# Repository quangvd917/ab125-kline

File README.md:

# AB125 K-Line: đọc dữ liệu ECU Honda Air Blade 125 (2023) qua giắc DLC

> **English summary.** DIY reader for the Honda K-Line diagnostic port on a Honda Air Blade 125 (2023, PGM-FI) scooter. An ESP32-C3 talks to the ECU through an L9637D transceiver, decodes RPM, speed, coolant/intake temperature, throttle and battery voltage from Honda table `0x17`, and shows them on a phone (WiFi web page) and on a 2.8" "Cheap Yellow Display" dashboard (ESP-NOW). Firmware (PlatformIO/Arduino), KiCad schematic + PCB, and the decoded protocol are all here. Docs are in Vietnamese.

## Tính năng
- Đọc **vòng tua, tốc độ, nhiệt độ máy, nhiệt độ khí nạp, độ mở bướm ga, điện áp ắc quy** khoảng 7 lần mỗi giây.
- **Trang web trên điện thoại:** kết nối WiFi `AB125`, mở `http://192.168.4.1`. Không cần cài app.
- **Đọc mã lỗi PGM-FI** (lỗi hiện tại và lỗi đã lưu) kèm mô tả tiếng Việt. Đã kiểm chứng bằng một lỗi thật tạo ra có chủ đích (8-1). Có nút **xóa lỗi** (đã thử thành công trên xe), chỉ hoạt động khi máy không nổ. Xem [protocol.md](docs/protocol.md#mã-lỗi-dtc).
- **Dashboard màn CYD 2.8"** nhận dữ liệu không dây qua ESP-NOW: đồng hồ RPM, tốc độ, cảnh báo nhiệt độ và điện áp.
- **Ghi log** dữ liệu thô ra file để phân tích.
- Mạch giao tiếp **L9637D** tự làm được trên PCB 1 mặt. File KiCad có đủ schematic và PCB.

## Sơ đồ hệ thống
```
 Giắc DLC trên xe            Mạch L9637D                ESP32-C3 SuperMini
 ┌──────────┐  +12V  ┌──────────────────────┐  5V/3V3  ┌──────────────────┐   WiFi AP "AB125"   ┌─────────┐
 │ +12V     ├───────►│ bảo vệ + lọc + MP1584 ├────────►│                  ├────────────────────►│ Điện    │
 │ K-Line   ├◄──────►│ L9637D (K ↔ TX/RX)   ├◄───────►│ firmware         │                     │ thoại   │
 │ GND      ├────────┤                      │ TX / RX │ kline-reader     │   ESP-NOW (kênh 1)  └─────────┘
 └──────────┘        └──────────────────────┘         └──────────────────┴────────────────────► Màn CYD 2.8"
```

## Cấu trúc repo
```
firmware/
  kline-reader/      firmware đọc K-Line (ESP32-C3 SuperMini, hoặc ESP32 + mạch 2N2222 v1)
  dashboard-cyd/     firmware dashboard cho màn CYD 2.8" (ESP32-2432S028R)
  common/            dash_packet.h: định dạng gói ESP-NOW dùng chung
  flash.sh           build + nạp, chọn đúng board theo địa chỉ MAC
hardware/
  kline-l9637d/      project KiCad: schematic, PCB, BOM, PDF
docs/
  protocol.md        giao thức Honda K-Line và cấu trúc bảng 0x17
  hardware.md        lắp ráp mạch L9637D, nối dây, kiểm tra trước khi cấp điện
  v1-discrete-circuit.md   mạch v1 dùng transistor 2N2222 (không cần IC)
  images/            ảnh mạch, dashboard, ảnh render PCB
  sample-logs/       log thật ghi trên xe (tắt máy, không tải, vặn ga, quay bánh)
```

## Bắt đầu nhanh
Cần cài [PlatformIO](https://platformio.org/) (bản dòng lệnh hoặc extension VS Code).

1. **Làm mạch:** theo [docs/hardware.md](docs/hardware.md). Nếu chưa có IC L9637D, có thể làm mạch v1 bằng transistor: [docs/v1-discrete-circuit.md](docs/v1-discrete-circuit.md).
2. **Khai báo MAC các board:** chép `firmware/boards.local.example` thành `firmware/boards.local` rồi điền MAC. Chạy `./flash.sh` sẽ in ra MAC của mọi board đang cắm.
3. **Nạp firmware:**
   ```bash
   cd firmware
   ./flash.sh -e c3_supermini     # bộ đọc K-Line (ESP32-C3 + L9637D)
   ./flash.sh -e cyd              # dashboard CYD (không bắt buộc)
   ```
4. **Thử trên bàn:** cấp 12V vào mạch. Log phải báo `INIT FAIL, code=0`: mạch đã chạy, chỉ thiếu ECU để trả lời.
5. **Cắm vào xe và bật khóa:** log báo `INIT OK`, rồi in các dòng `rpm=… km/h=…`.

Chi tiết từng phần:
- [firmware/kline-reader/README.md](firmware/kline-reader/README.md)
- [firmware/dashboard-cyd/README.md](firmware/dashboard-cyd/README.md)
- [hardware/kline-l9637d/README.md](hardware/kline-l9637d/README.md)

## Giao thức
Honda dùng K-Line 10400 baud với tập lệnh riêng, **không phải OBD2**, nên ELM327 không đọc được. Phần đánh thức ECU, cách đọc bảng và ý nghĩa từng byte của bảng `0x17` (đã kiểm chứng trên xe) xem ở [docs/protocol.md](docs/protocol.md).

## ⚠️ Lưu ý an toàn
- Đây là dự án cá nhân, đã thử trên **một** xe Air Blade 125 đời 2023. Các đời xe khác có thể khác cấu trúc bảng dữ liệu.
- Firmware chỉ gửi lệnh **đọc**, không ghi gì vào ECU.
- Lắp **cầu chì 1A** trên dây 12V. Không chập các chân của giắc DLC.
- **Không xem màn hình khi đang chạy xe.**
- Bạn tự chịu trách nhiệm khi can thiệp vào hệ thống điện của xe.

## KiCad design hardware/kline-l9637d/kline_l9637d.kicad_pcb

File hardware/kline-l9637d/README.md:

# kline-l9637d: mạch giao tiếp K-Line (KiCad)

Mở `kline_l9637d.kicad_pro` bằng **KiCad 9 hoặc 10**. Symbol của L9637D nằm sẵn trong project, ở file `kline.kicad_sym` (khai báo qua `sym-lib-table`). Không cần cài thêm thư viện.

| File | Nội dung |
|---|---|
| `kline_l9637d.kicad_sch` | Schematic |
| `kline_l9637d.kicad_pcb` | PCB 1 mặt (lớp B.Cu) để tự làm mạch |
| `kline_l9637d_schematic.pdf` | Bản PDF của schematic |
| `bom.csv` | Danh sách linh kiện |

**Kết quả kiểm tra:**
- ERC: 0 lỗi.
- DRC: 0 lỗi, 0 pad chưa nối. Còn lại vài cảnh báo: footprint đã được chỉnh pad để dễ làm mạch tự chế, và silkscreen chồng lên pad.

Hướng dẫn lắp ráp và kiểm tra: [docs/hardware.md](../../docs/hardware.md).

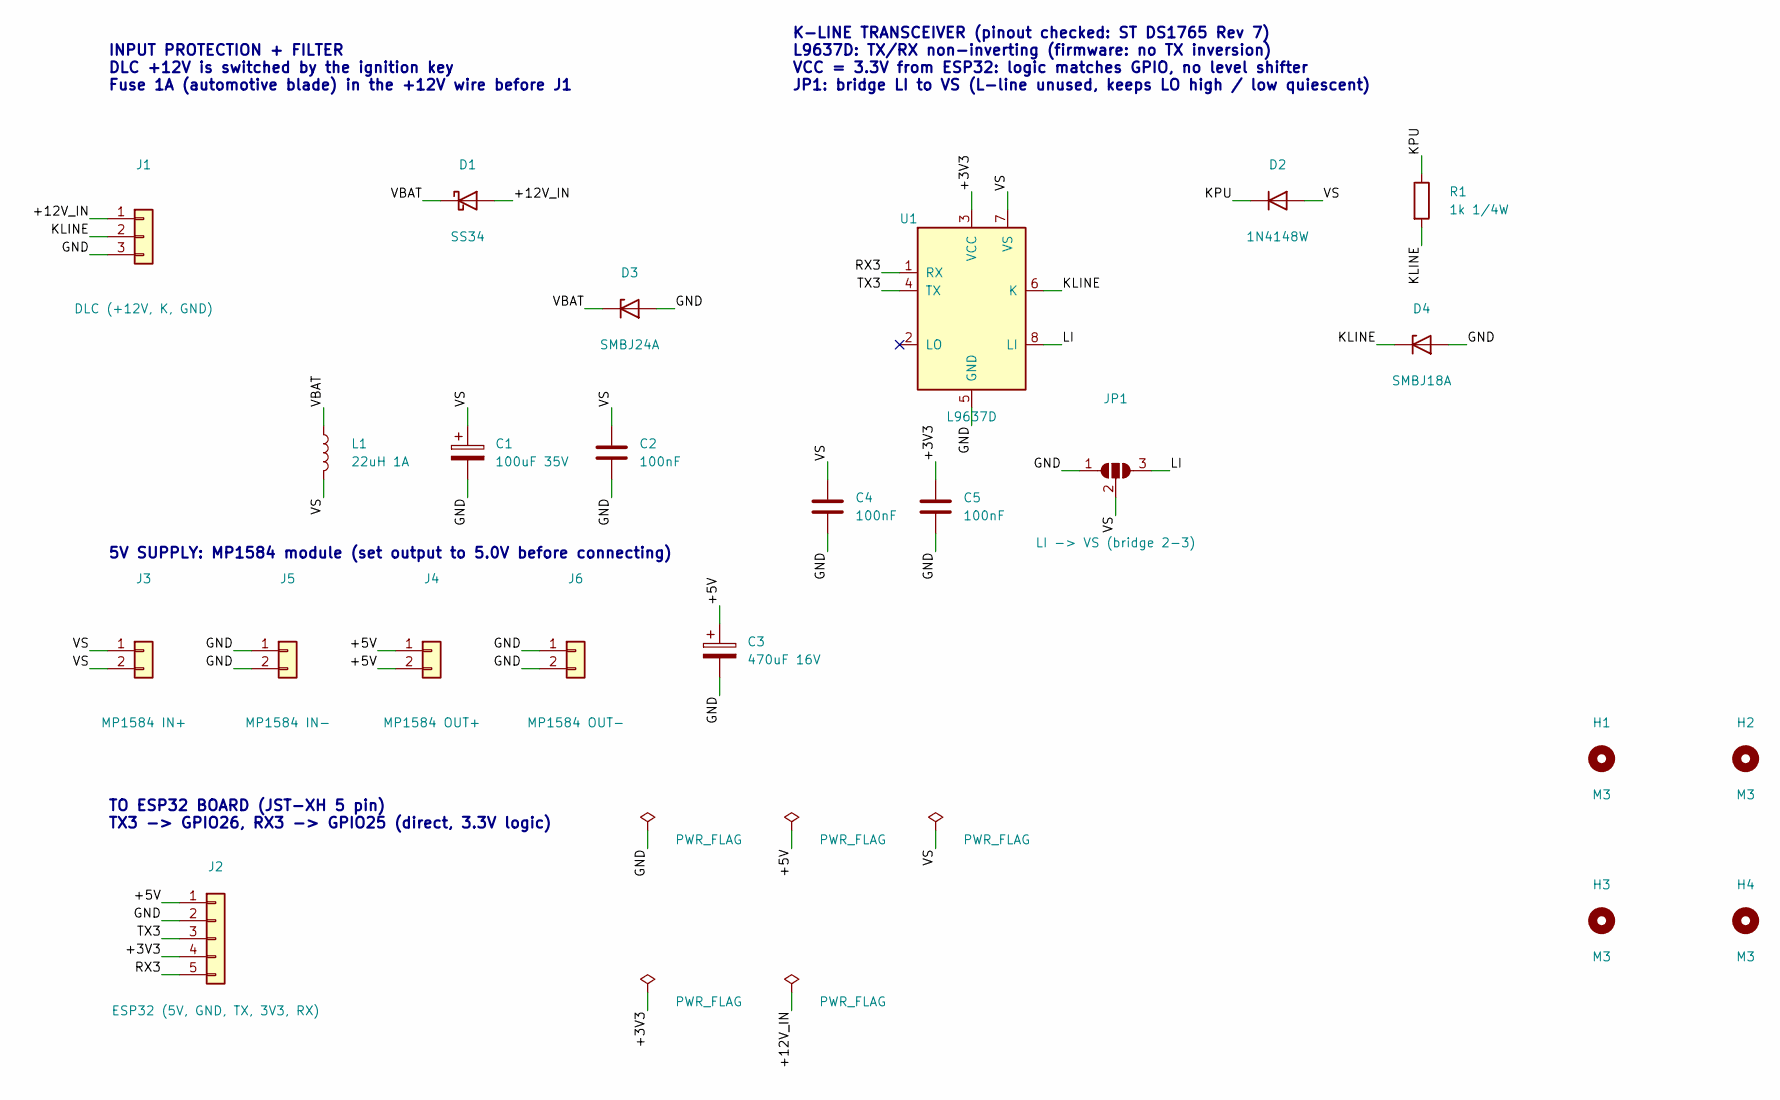
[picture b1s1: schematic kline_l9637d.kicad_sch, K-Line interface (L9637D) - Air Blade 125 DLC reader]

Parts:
C1: 100uF 35V; CP_Radial_D6.3mm_P2.50mm
C2, C4, C5: 100nF; C_1206_3216Metric_Pad1.33x1.80mm_HandSolder
C3: 470uF 16V; CP_Elec_8x10
D1: SS34; D_SMA
D2: 1N4148W; D_SOD-123
D3: SMBJ24A; D_SMB
D4: SMBJ18A; D_SMB
H1, H2, H3, H4: M3; MountingHole_3.2mm_M3
J1: DLC (+12V, K, GND); JST_XH_S3B-XH-A_1x03_P2.50mm_Horizontal
J2: ESP32 (5V, GND, TX, 3V3, RX); JST_XH_S5B-XH-A_1x05_P2.50mm_Horizontal
J3: MP1584 IN+; PinHeader_1x02_P2.54mm_Vertical
J4: MP1584 OUT+; PinHeader_1x02_P2.54mm_Vertical
J5: MP1584 IN-; PinHeader_1x02_P2.54mm_Vertical
J6: MP1584 OUT-; PinHeader_1x02_P2.54mm_Vertical
JP1: LI -> VS (bridge 2-3); SolderJumper-3_P1.3mm_Open_RoundedPad1.0x1.5mm
L1: 22uH 1A; L_Changjiang_FXL0630
R1: 1k 1/4W; R_1206_3216Metric_Pad1.30x1.75mm_HandSolder
U1: L9637D; SOIC-8_3.9x4.9mm_P1.27mm

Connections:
/+3V3: C5.1, J2.4, U1.3 (VCC)
/+5V: C3.1, J2.1, J4.1, J4.2
/+12V_IN: D1.2 (A), J1.1
/GND: C1.2, C2.2, C3.2, C4.2, C5.2, D3.2 (A), D4.2 (A), J1.3, J2.2, J5.1, J5.2, J6.1, J6.2, JP1.1 (A), U1.5 (GND)
/KLINE: D4.1 (K), J1.2, R1.2, U1.6 (K)
/KPU: D2.1 (K), R1.1
/LI: JP1.3 (B), U1.8 (LI)
/RX3: J2.5, U1.1 (RX)
/TX3: J2.3, U1.4 (TX)
/VBAT: D1.1 (K), D3.1 (K), L1.1
/VS: C1.1, C2.1, C4.1, D2.2 (A), J3.1, J3.2, JP1.2 (C), L1.2, U1.7 (VS)

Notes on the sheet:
K-LINE TRANSCEIVER (pinout checked: ST DS1765 Rev 7) L9637D: TX/RX non-inverting (firmware: no TX inversion) VCC = 3.3V from ESP32: logic matches GPIO, no level shifter JP1: bridge LI to VS (L-line unused, keeps LO high / low quiescent)
5V SUPPLY: MP1584 module (set output to 5.0V before connecting)
INPUT PROTECTION + FILTER DLC +12V is switched by the ignition key Fuse 1A (automotive blade) in the +12V wire before J1
TO ESP32 BOARD (JST-XH 5 pin) TX3 -> GPIO26, RX3 -> GPIO25 (direct, 3.3V logic)

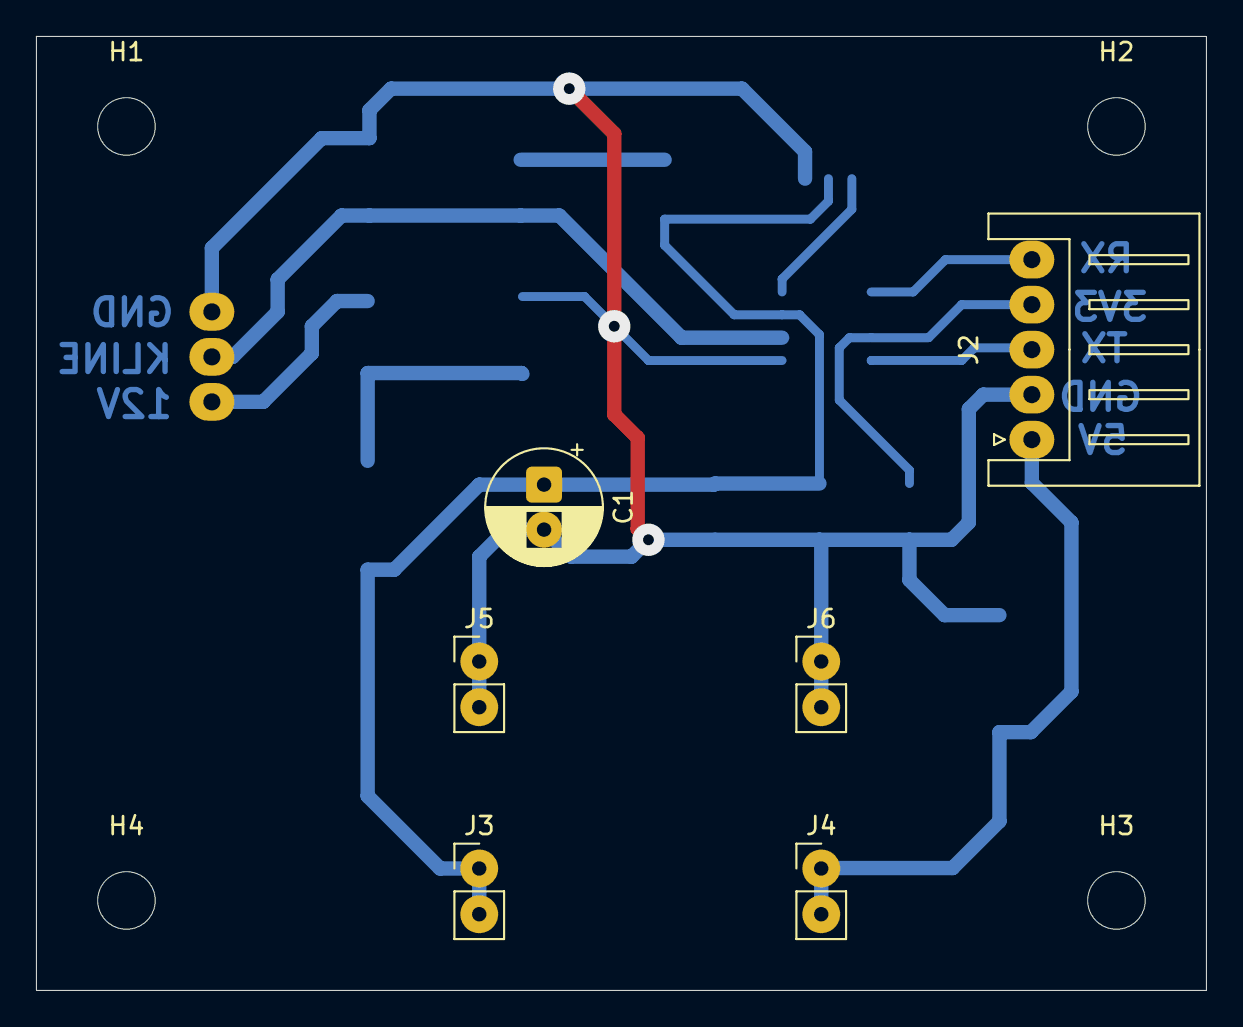
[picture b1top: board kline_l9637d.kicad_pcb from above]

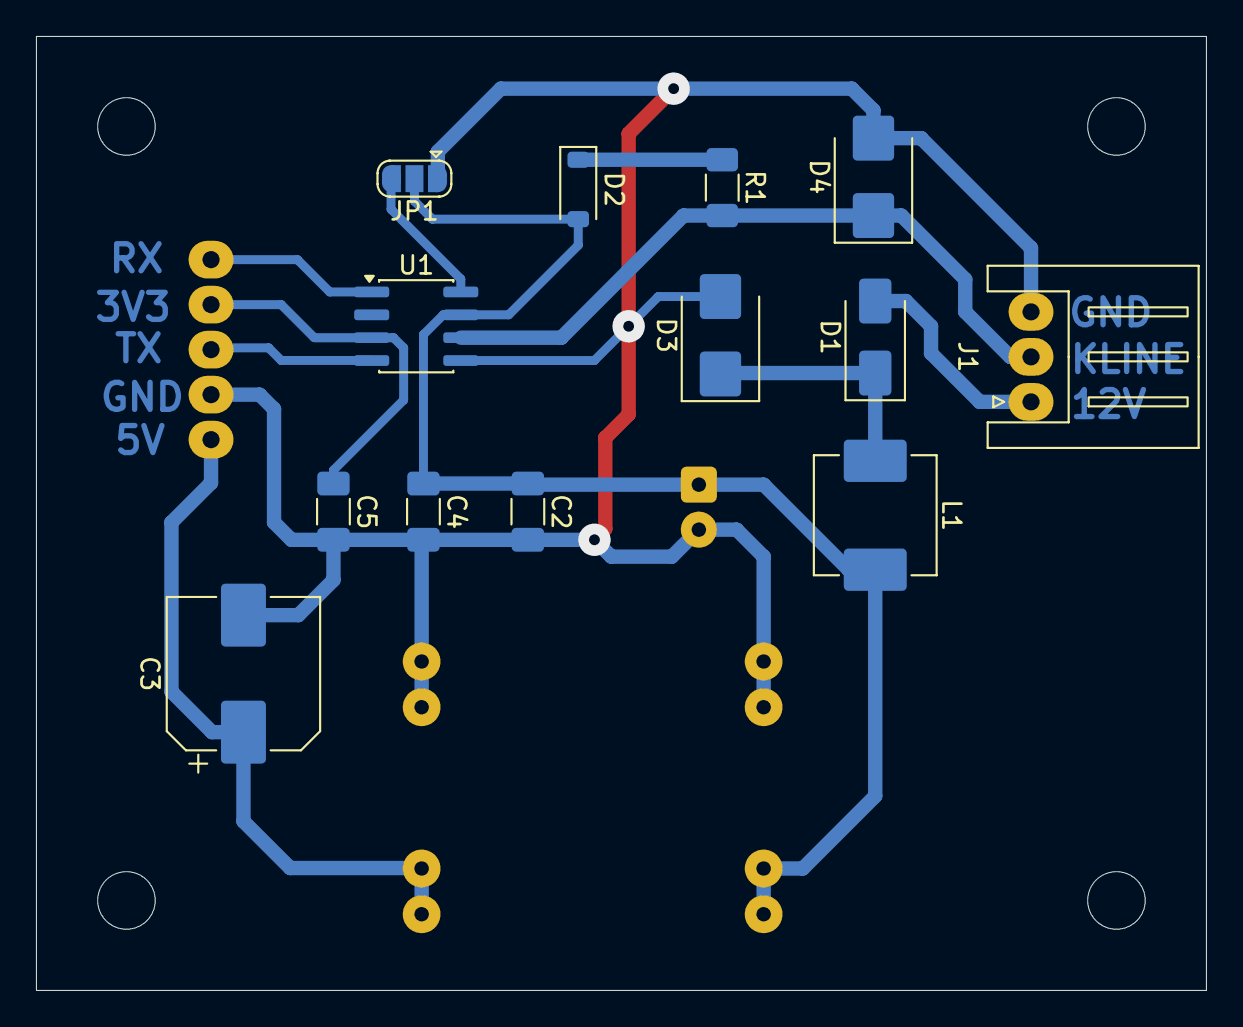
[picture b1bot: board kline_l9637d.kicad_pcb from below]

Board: 2 copper layers, 65.0 x 53.0 mm, 23 parts (13 on the bottom side), 11 nets.

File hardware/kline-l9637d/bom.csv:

"Ref","Value","Footprint","Qty"
"C1","100uF 35V","Capacitor_THT:CP_Radial_D6.3mm_P2.50mm","1"
"C2,C4,C5","100nF","Capacitor_SMD:C_1206_3216Metric_Pad1.33x1.80mm_HandSolder","3"
"C3","470uF 16V","Capacitor_SMD:CP_Elec_8x10","1"
"D1","SS34","Diode_SMD:D_SMA","1"
"D2","1N4148W","Diode_SMD:D_SOD-123","1"
"D3","SMBJ24A","Diode_SMD:D_SMB","1"
"D4","SMBJ18A","Diode_SMD:D_SMB","1"
"H1-H4","M3","MountingHole:MountingHole_3.2mm_M3","4"
"J1","DLC (+12V, K, GND)","Connector_JST:JST_XH_S3B-XH-A_1x03_P2.50mm_Horizontal","1"
"J2","ESP32 (5V, GND, TX, 3V3, RX)","Connector_JST:JST_XH_S5B-XH-A_1x05_P2.50mm_Horizontal","1"
"J3","MP1584 IN+","Connector_PinHeader_2.54mm:PinHeader_1x02_P2.54mm_Vertical","1"
"J4","MP1584 OUT+","Connector_PinHeader_2.54mm:PinHeader_1x02_P2.54mm_Vertical","1"
"J5","MP1584 IN-","Connector_PinHeader_2.54mm:PinHeader_1x02_P2.54mm_Vertical","1"
"J6","MP1584 OUT-","Connector_PinHeader_2.54mm:PinHeader_1x02_P2.54mm_Vertical","1"
"JP1","LI -> VS (bridge 2-3)","Jumper:SolderJumper-3_P1.3mm_Open_RoundedPad1.0x1.5mm","1"
"L1","22uH 1A","Inductor_SMD:L_Changjiang_FXL0630","1"
"R1","1k 1/4W","Resistor_SMD:R_1206_3216Metric_Pad1.30x1.75mm_HandSolder","1"
"U1","L9637D","Package_SO:SOIC-8_3.9x4.9mm_P1.27mm","1"
